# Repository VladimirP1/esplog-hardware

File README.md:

### What is this
These are boards for running the [esp-gyrologger](https://github.com/VladimirP1/esp-gyrologger) firmware. They contain an esp32-c3, a mems IMU and 3.3v a regulator. Wi-Fi antenna is bad, but it works at low TX power.

esplog-hv accepts 4-30v input

esplog-ldo accepts 4-6v input

### How the finished product look like
This is how esplog_ldo and esplog_hv look like

</img>

</img>

</img>

</img>

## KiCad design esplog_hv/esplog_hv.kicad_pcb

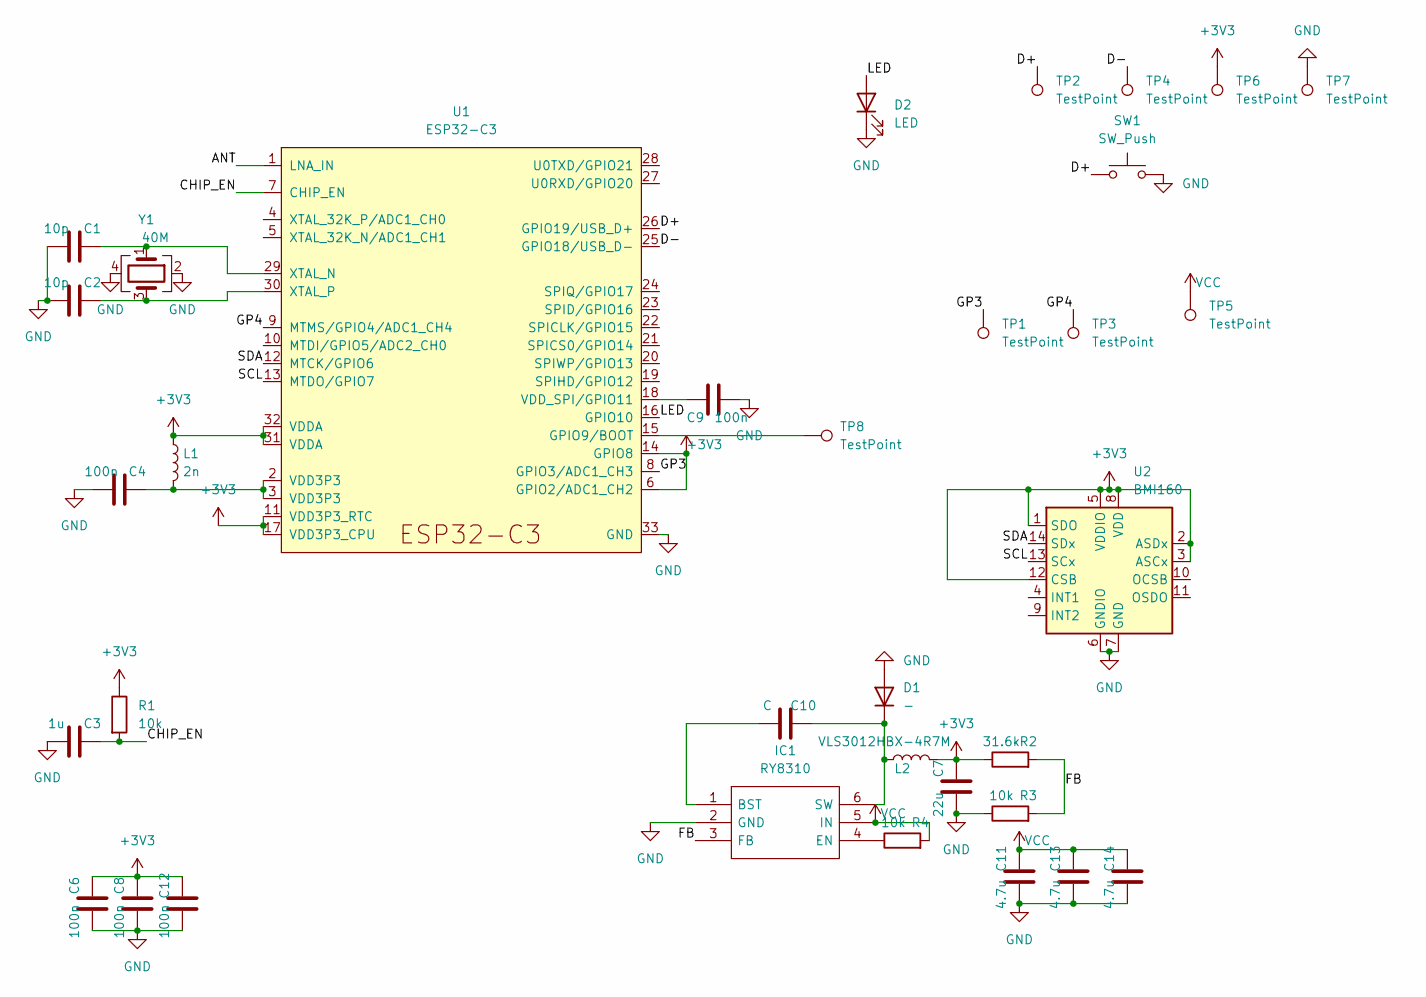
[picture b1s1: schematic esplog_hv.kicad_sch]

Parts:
C1, C2: 10p; C_0402_1005Metric
C3: 1u; C_0402_1005Metric
C4, C6, C8, C9, C12: 100n; C_0402_1005Metric
C7: 22u; C_0603_1608Metric
C10: C; C_0402_1005Metric
C11, C13, C14: 4.7u; C_0603_1608Metric
D1: -; D_SOD-523
D2: LED; LED_0603_1608Metric
IC1: RY8310; SOT-23-6; Mouser Part Number 946-MP2359DJLFZ
L1: 2n; L_0402_1005Metric
L2: VLS3012HBX-4R7M; VLS3012
R1, R3, R4: 10k; R_0402_1005Metric
R2: 31.6k; R_0402_1005Metric
SW1: SW_Push; SW_SPST_PTS810
TP1, TP2, TP3, TP4, TP5, TP6, TP7, TP8: TestPoint; TestPoint_Pad_1.0x1.0mm
U1: ESP32-C3; QFN-32-1EP_5x5mm_P0.5mm_EP3.45x3.45mm
U2: BMI160; Bosch_LGA-14_3x2.5mm_P0.5mm
Y1: 40M; Crystal_SMD_3225-4Pin_3.2x2.5mm

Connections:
+3V3: C6.2, C7.2, C8.2, C12.2, L1.1, L2.2, R1.1, R2.1, TP6.1, U1.6 (GPIO2/ADC1_CH2), U1.11 (VDD3P3_RTC), U1.14 (GPIO8), U1.17 (VDD3P3_CPU), U1.31 (VDDA), U1.32 (VDDA), U2.1 (SDO), U2.2 (ASDx), U2.3 (ASCx), U2.5 (VDDIO), U2.8 (VDD), U2.12 (CSB)
/ANT: U1.1 (LNA_IN)
/CHIP_EN: C3.2, R1.2, U1.7 (CHIP_EN)
/D+: SW1.1, TP2.1, U1.26 (GPIO19/USB_D+)
/D-: TP4.1, U1.25 (GPIO18/USB_D-)
/FB: IC1.3 (FB), R2.2, R3.2
/GP3: TP1.1, U1.8 (GPIO3/ADC1_CH3)
/GP4: TP3.1, U1.9 (MTMS/GPIO4/ADC1_CH4)
/LED: D2.2 (A), U1.16 (GPIO10)
/SCL: U1.13 (MTDO/GPIO7), U2.13 (SCx)
/SDA: U1.12 (MTCK/GPIO6), U2.14 (SDx)
GND: C1.1, C2.1, C3.1, C4.1, C6.1, C7.1, C8.1, C9.1, C11.1, C12.1, C13.1, C14.1, D1.2 (A), D2.1 (K), IC1.2 (GND), R3.1, SW1.2, TP7.1, U1.33 (GND), U2.6 (GNDIO), U2.7 (GND), Y1.2, Y1.4
unnamed: C1.2, U1.29 (XTAL_N), Y1.1
unnamed: C2.2, U1.30 (XTAL_P), Y1.3
unnamed: C4.2, L1.2, U1.2 (VDD3P3), U1.3 (VDD3P3)
unnamed: C9.2, U1.18 (VDD_SPI/GPIO11)
unnamed: C10.1, IC1.1 (BST)
unnamed: C10.2, D1.1 (K), IC1.6 (SW), L2.1
unnamed: IC1.4 (EN), R4.1
unnamed: TP8.1, U1.15 (GPIO9/BOOT)
VCC: C11.2, C13.2, C14.2, IC1.5 (IN), R4.2, TP5.1

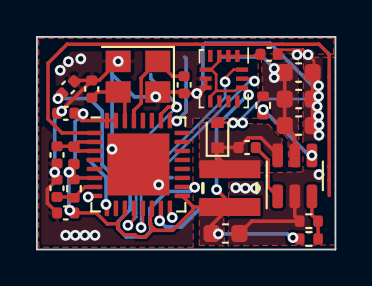
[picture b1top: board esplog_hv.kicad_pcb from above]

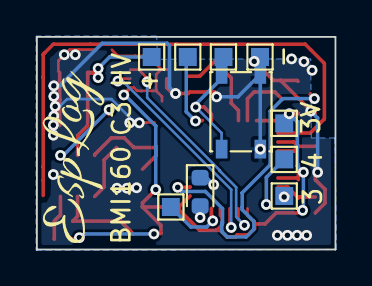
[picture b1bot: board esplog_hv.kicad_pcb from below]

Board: 2 copper layers, 16.6 x 11.8 mm, 34 parts (10 on the bottom side), 20 nets.

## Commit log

2022-08-30 Remove ground polygon under antenna
2022-08-30 Add component values
2022-11-01 esplog_hv: change the capacitor value on chip_en to 1u
2022-11-02 add gerbers for esplog-hv
2023-09-07 add readme
2023-09-07 upd readme
